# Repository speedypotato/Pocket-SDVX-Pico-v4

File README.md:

# Pocket-SDVX-Pico-v4
Pocket SDVX Pico v4 source files, production files, and documentation

This work is licensed under a Creative Commons Attribution-NonCommercial-ShareAlike 4.0 International License.  中国人，我在看你们。

Although I won't be selling this particular version anymore, I have plans to sell updated designs soon.  Join the discord for discussion and support! https://discord.gg/MmuKd73XbY . I also now have a storefront! https://www.speedylabs.us/

## Parts Required:
- JLCPCB parts (Boards are 180 mm*100 mm, white PCB color, remove order number[specify a location]):
    - 1x Pocket-SDVX-Pico-Plate-v4-2 (MOQ 5)
    - 1x Pocket-SDVX-Pico-v4-3 + SMT Assembly (MOQ 5)
        - SMT Assemble the top side.  There should be 9 unique parts.
- McMaster parts:
    - 4x Feet - 8884T13
    - 4x M3 Lock Nut - 90576A102
    - 4x M3x12 Screw - 92095A183 
    - 4x No.6 1/8" Nylon Spacer - 94639A507 
- Mouser parts:
    - 2x 2U Stabilizer - 540-G99-0224
    - 2x Encoder - PEC16-4015F-N0024
- 1x Raspberry Pi Pico
- XDA Keycap Set https://www.speedylabs.us/product/pocket-sdvx-keycaps/
    - 1x 1u, 4x 1.5u, 2x 2u
- 2x 22mm Knob https://www.speedylabs.us/product/pocket-sdvx-aluminum-knob/
- 7x Gateron Yellow Switches (GATERON KS-9 or any switch with LED cutout)
- 7x Gateron Hotswap Sockets
- 1x 3D printed case, White PETG https://www.speedylabs.us/product/pocket-sdvx-pico-case/

[Pocket SDVX Pico v4 Quick Start Guide](https://docs.google.com/document/d/1lTzADQI5E5vRpHBv-0IfLbDSh2zEKCUAdh5BqFhex2I/edit?usp=sharing)  
[Kit Assembly Guide](https://docs.google.com/document/d/1bsWk7fmLKUGv5YgQknoNQcy0RX3fi5gCZRvfOJAa-P0/)

## Addendum
As promised many months ago, Speedy Labs' most popular product is now open sourced.  Pocket-SDVX-Pico v4 is my second PCB, and therefore everything's a little bit sloppy.  Nevertheless, everything here is functional and has been self-learned online along with the help of the community.  Thanks for all the support!

FYI I should probably let everyone know the most common defects I've received:
- RGB LEDs dead or not soldered properly
- Extra Aux Button wobbly/non-functional/misaligned
- Smudged Silkscreen

There's probably a 5% chance of this happening according to my statistics.  Nothing you can do about it aside from repairing it yourself.

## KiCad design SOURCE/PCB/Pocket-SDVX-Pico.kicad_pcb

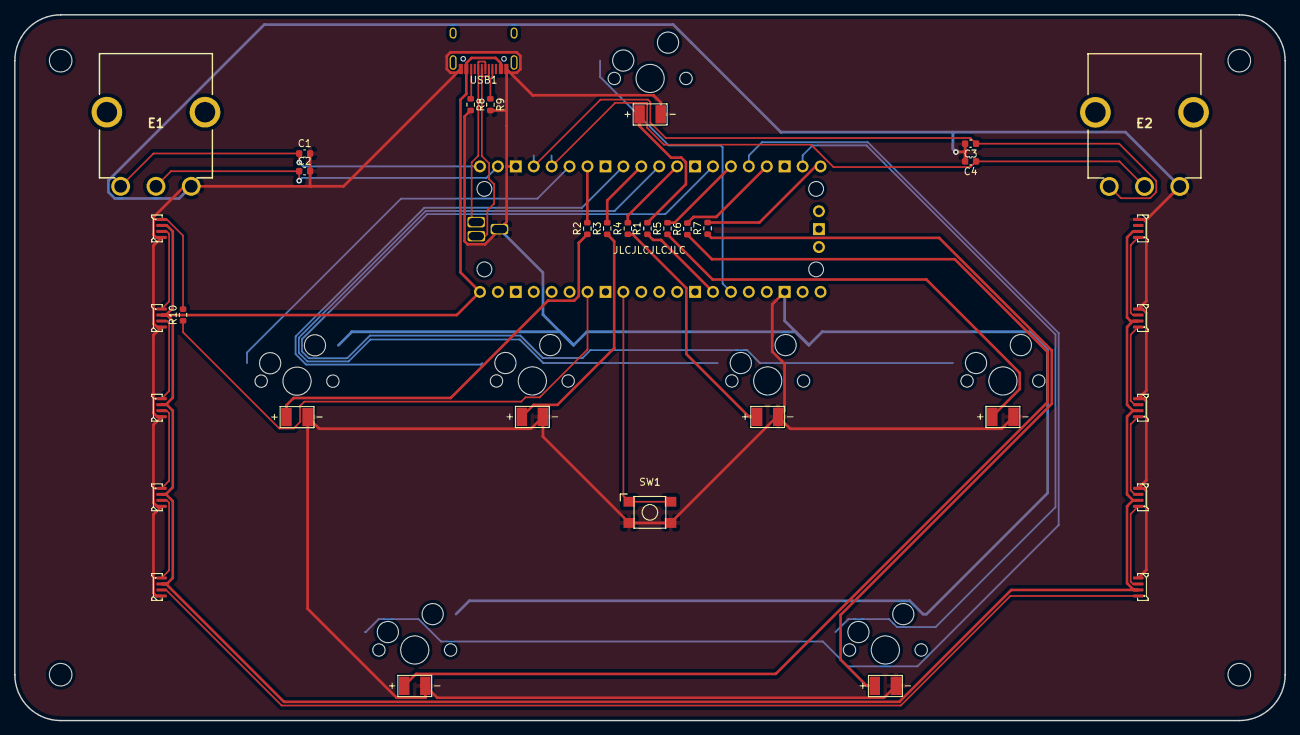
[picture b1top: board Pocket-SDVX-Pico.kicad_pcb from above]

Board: 2 copper layers, 180.0 x 100.0 mm, 36 parts (1 on the bottom side), 43 nets.

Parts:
C1, C2, C3, C4: 10nF; C_0603_1608Metric
E1, E2: PEC16-4015F-N0024; PEC16-4015F-N0024-millmax
LED1, LED2, LED3, LED4, LED5, LED6, LED7, LED8, LED9, LED10: WS2812B-4020
MX1: MX-LED-B; MXOnly-1.5U-Hotswap-LED-SMD
MX2, MX3, MX4, MX5: MX-LED; MXOnly-1.5U-Hotswap-LED-SMD
MX6, MX7: MX-LED-R; MXOnly-1.5U-Hotswap-LED-SMD
R1, R2, R3, R4, R5, R6, R7, R10: 220R; R_0603_1608Metric
R8, R9: 5K1; R_0603_1608Metric
SW1: KAN4542-0701C
U1: Pico; RPi_Pico_SMD_TH
USB1: HRO-TYPE-C-31-M-12; HRO-TYPE-C-31-M-12-Assembly

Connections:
+5V: LED1.2, LED2.2, LED3.2, LED4.2, LED5.2, LED6.2, LED7.2, LED8.2, LED9.2, LED10.2, U1.40, USB1.2, USB1.11
GND: C1.2, C2.2, C3.2, C4.2, E1.C1, E2.C1, LED1.4, LED2.4, LED3.4, LED4.4, LED5.4, LED6.4, LED7.4, LED8.4, LED9.4, LED10.4, MX1.2, MX1.4, MX2.2, MX2.4, MX3.2, MX3.4, MX4.2, MX4.4, MX5.2, MX5.4, MX6.2, MX6.4, MX7.2, MX7.4, R8.2, R9.2, SW1.3, SW1.4, U1.3, U1.23, U1.TP1, USB1.1, USB1.12
unnamed: C1.1, E1.A1, U1.1
unnamed: C2.1, E1.B1, U1.2
unnamed: C3.1, E2.A1, U1.4
unnamed: C4.1, E2.B1, U1.5
unnamed: LED1.1, R10.2
unnamed: LED1.3, LED2.1
unnamed: LED2.3, LED3.1
unnamed: LED3.3, LED4.1
unnamed: LED4.3, LED5.1
unnamed: LED5.3, LED6.1
unnamed: LED6.3, LED7.1
unnamed: LED7.3, LED8.1
unnamed: LED8.3, LED9.1
unnamed: LED9.3, LED10.1
unnamed: MX1.1, U1.26
unnamed: MX1.3, R1.1
unnamed: MX2.1, U1.6
unnamed: MX2.3, R2.1
unnamed: MX3.1, U1.9
unnamed: MX3.3, R3.1
unnamed: MX4.1, U1.11
unnamed: MX4.3, R4.1
unnamed: MX5.1, U1.14
unnamed: MX5.3, R5.1
unnamed: MX6.1, U1.16
unnamed: MX6.3, R6.1
unnamed: MX7.1, U1.19
unnamed: MX7.3, R7.1
unnamed: R1.2, U1.27
unnamed: R2.2, U1.7
unnamed: R3.2, U1.10
unnamed: R4.2, U1.12
unnamed: R5.2, U1.15
unnamed: R6.2, U1.17
unnamed: R7.2, U1.20
unnamed: R8.1, USB1.10
unnamed: R9.1, USB1.4
unnamed: R10.1, U1.34
unnamed: SW1.1, SW1.2, U1.32
unnamed: U1.TP2, USB1.5, USB1.7
unnamed: U1.TP3, USB1.6, USB1.8

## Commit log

2022-03-30 v4.3 | Pocket SDVX Pico Release
2022-03-30 Image Upload
2022-04-08 Update README.md
    Clarified SMT
2022-04-08 Update README.md
    Defects
